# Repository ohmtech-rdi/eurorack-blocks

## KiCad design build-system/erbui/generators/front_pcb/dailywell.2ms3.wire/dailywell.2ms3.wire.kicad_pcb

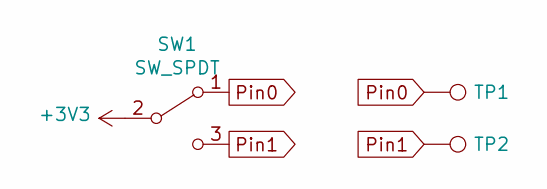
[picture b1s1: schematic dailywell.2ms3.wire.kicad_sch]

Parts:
SW1: SW_SPDT; SW_SPDT_Dailywell
TP1, TP2: TestPoint; TestPoint_Pad_D1.5mm

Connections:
+3V3: SW1.2 (B)
Pin0: SW1.1 (A), TP1.1
Pin1: SW1.3 (C), TP2.1

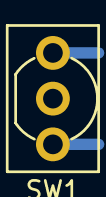
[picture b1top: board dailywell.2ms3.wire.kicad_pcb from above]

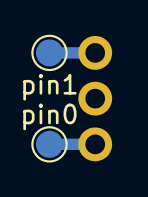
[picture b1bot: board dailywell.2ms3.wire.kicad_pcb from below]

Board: 2 copper layers, 3 parts (2 on the bottom side), 2 nets.

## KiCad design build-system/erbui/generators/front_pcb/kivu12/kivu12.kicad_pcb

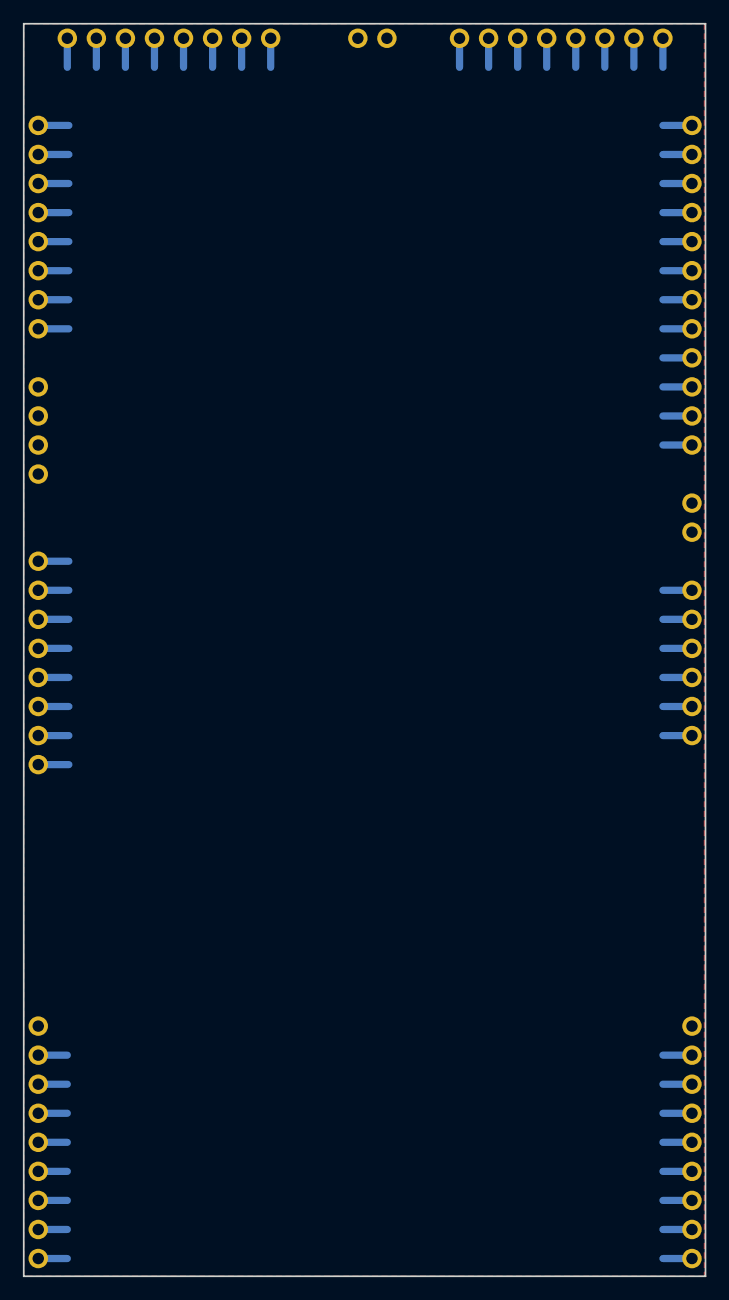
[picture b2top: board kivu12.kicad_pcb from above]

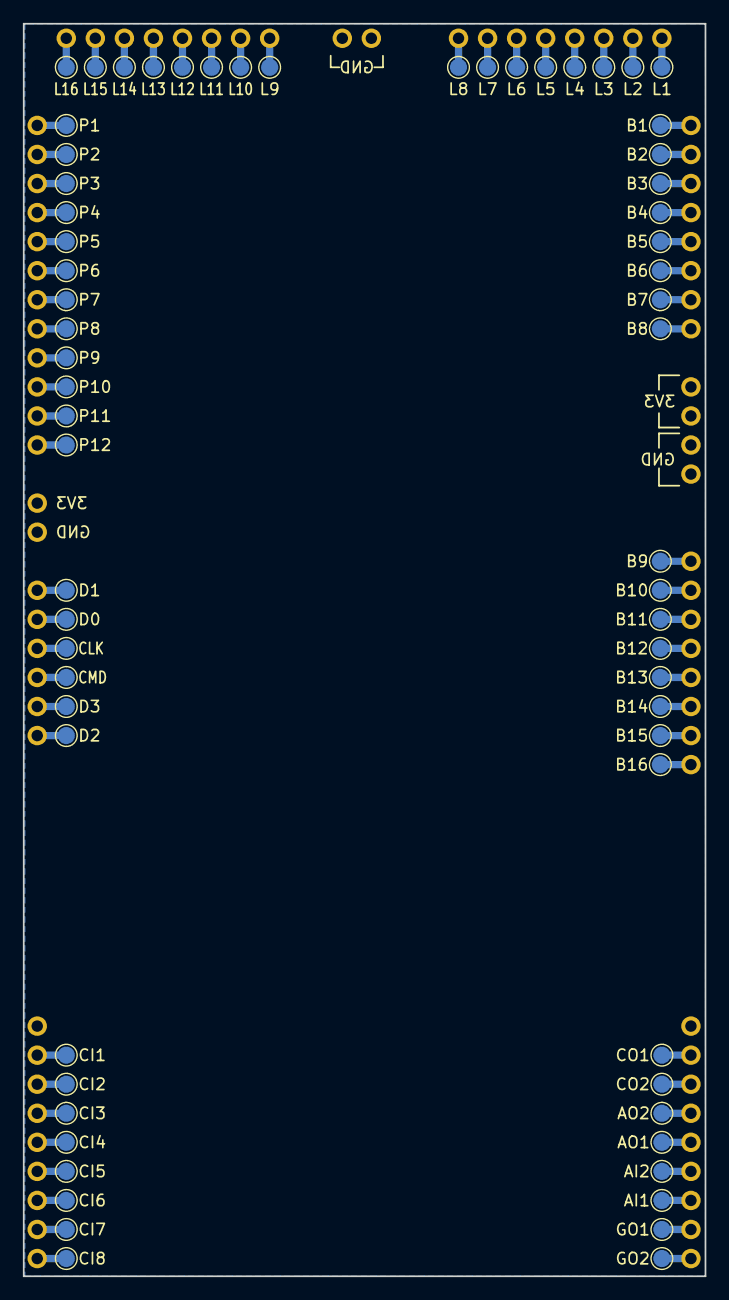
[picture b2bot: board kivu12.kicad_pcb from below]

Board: 2 copper layers, 59.6 x 109.5 mm, 77 parts (77 on the bottom side), 68 nets.

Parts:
AI1, AI2: TestPoint; TestPoint_Pad_D1.5mm
AO1, AO2: TestPoint; TestPoint_Pad_D1.5mm
B1, B2, B3, B4, B5, B6, B7, B8, B9, B10, B11, B12, B13, B14, B15, B16: TestPoint; TestPoint_Pad_D1.5mm
CI1, CI2, CI3, CI4, CI5, CI6, CI7, CI8: TestPoint; TestPoint_Pad_D1.5mm
CO1, CO2: TestPoint; TestPoint_Pad_D1.5mm
GO1, GO2: TestPoint; TestPoint_Pad_D1.5mm
J6: POWER2; PinHeader_1x04_P2.54mm_Vertical
J9: POWER1; PinHeader_1x02_P2.54mm_Vertical
J11: GND; PinHeader_1x02_P2.54mm_Vertical
L1, L2, L3, L4, L5, L6, L7, L8, L9, L10, L11, L12, L13, L14, L15, L16: TestPoint; TestPoint_Pad_D1.5mm
P1, P2, P3, P4, P5, P6, P7, P8, P9, P10, P11, P12: TestPoint; TestPoint_Pad_D1.5mm
SDCLK1: TestPoint; TestPoint_Pad_D1.5mm
SDCMD1: TestPoint; TestPoint_Pad_D1.5mm
SDD0, SDD1, SDD2, SDD3: TestPoint; TestPoint_Pad_D1.5mm
ZZ1: PX; PinHeader_1x12_P2.54mm_Vertical
ZZ2: CIX; PinHeader_1x09_P2.54mm_Vertical
ZZ3, ZZ7: BX; PinHeader_1x08_P2.54mm_Vertical
ZZ4, ZZ12: LX; PinHeader_1x08_P2.54mm_Vertical
ZZ5: ANALOG; PinHeader_1x09_P2.54mm_Vertical
ZZ10: SD; PinHeader_1x06_P2.54mm_Vertical

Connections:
+3V3: J6.1, J6.2, J9.1
GND: J6.3, J6.4, J9.2, J11.1, J11.2, ZZ2.1, ZZ5.1
unnamed: AI1.1, ZZ5.7
unnamed: AI2.1, ZZ5.6
unnamed: AO1.1, ZZ5.5
unnamed: AO2.1, ZZ5.4
unnamed: B1.1, ZZ3.1
unnamed: B2.1, ZZ3.2
unnamed: B3.1, ZZ3.3
unnamed: B4.1, ZZ3.4
unnamed: B5.1, ZZ3.5
unnamed: B6.1, ZZ3.6
unnamed: B7.1, ZZ3.7
unnamed: B8.1, ZZ3.8
unnamed: B9.1, ZZ7.1
unnamed: B10.1, ZZ7.2
unnamed: B11.1, ZZ7.3
unnamed: B12.1, ZZ7.4
unnamed: B13.1, ZZ7.5
unnamed: B14.1, ZZ7.6
unnamed: B15.1, ZZ7.7
unnamed: B16.1, ZZ7.8
unnamed: CI1.1, ZZ2.2
unnamed: CI2.1, ZZ2.3
unnamed: CI3.1, ZZ2.4
unnamed: CI4.1, ZZ2.5
unnamed: CI5.1, ZZ2.6
unnamed: CI6.1, ZZ2.7
unnamed: CI7.1, ZZ2.8
unnamed: CI8.1, ZZ2.9
unnamed: CO1.1, ZZ5.2
unnamed: CO2.1, ZZ5.3
unnamed: GO1.1, ZZ5.8
unnamed: GO2.1, ZZ5.9
unnamed: L1.1, ZZ4.1
unnamed: L2.1, ZZ4.2
unnamed: L3.1, ZZ4.3
unnamed: L4.1, ZZ4.4
unnamed: L5.1, ZZ4.5
unnamed: L6.1, ZZ4.6
unnamed: L7.1, ZZ4.7
unnamed: L8.1, ZZ4.8
unnamed: L9.1, ZZ12.1
unnamed: L10.1, ZZ12.2
unnamed: L11.1, ZZ12.3
unnamed: L12.1, ZZ12.4
unnamed: L13.1, ZZ12.5
unnamed: L14.1, ZZ12.6
unnamed: L15.1, ZZ12.7
unnamed: L16.1, ZZ12.8
unnamed: P1.1, ZZ1.1
unnamed: P2.1, ZZ1.2
unnamed: P3.1, ZZ1.3
unnamed: P4.1, ZZ1.4
unnamed: P5.1, ZZ1.5
unnamed: P6.1, ZZ1.6
unnamed: P7.1, ZZ1.7
unnamed: P8.1, ZZ1.8
unnamed: P9.1, ZZ1.9
unnamed: P10.1, ZZ1.10
unnamed: P11.1, ZZ1.11
unnamed: P12.1, ZZ1.12
unnamed: SDCLK1.1, ZZ10.3
unnamed: SDCMD1.1, ZZ10.4
unnamed: SDD0.1, ZZ10.2
unnamed: SDD1.1, ZZ10.1
unnamed: SDD2.1, ZZ10.6
unnamed: SDD3.1, ZZ10.5

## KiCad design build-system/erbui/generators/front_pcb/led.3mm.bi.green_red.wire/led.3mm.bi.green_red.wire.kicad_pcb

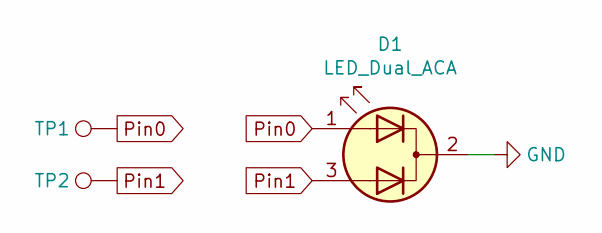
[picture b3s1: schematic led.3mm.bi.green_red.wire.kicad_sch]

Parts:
D1: LED_Dual_ACA; LED_D3.0mm-3
TP1, TP2: TestPoint; TestPoint_Pad_D1.5mm

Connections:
GND: D1.2 (K)
Pin0: D1.1 (A1), TP1.1
Pin1: D1.3 (A2), TP2.1

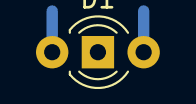
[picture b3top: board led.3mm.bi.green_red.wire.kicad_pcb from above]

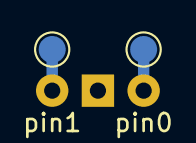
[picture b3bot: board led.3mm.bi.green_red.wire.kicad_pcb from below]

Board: 2 copper layers, 3 parts (2 on the bottom side), 2 nets.

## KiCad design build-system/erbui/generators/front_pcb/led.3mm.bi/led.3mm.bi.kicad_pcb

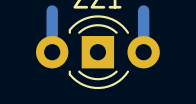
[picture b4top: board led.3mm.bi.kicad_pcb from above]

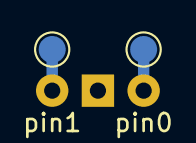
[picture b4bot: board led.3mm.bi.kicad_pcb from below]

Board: 2 copper layers, 3 parts (2 on the bottom side), 2 nets.

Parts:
Pin0, Pin1: TestPoint; TestPoint_Pad_D1.5mm
ZZ1: LED_Dual_ACA; LED_D3.0mm-3

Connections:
unnamed: Pin0.1, ZZ1.1
unnamed: Pin1.1, ZZ1.3
